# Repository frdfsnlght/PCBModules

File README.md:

# PCBModules
A set of KiCAD 6 schematics and PCB layouts for some handy modules used for electronics projects.

## Available modules

* 8PinHeader

   Useful for plugging in half of a ESP32 CAM module. Includes 2 mounting holes.

* 19PinHeader

   Useful for plugging in half of a typical ESP32 Dev module. Includes 2 mounting holes.

* DrokPowerSupply

   Mount a [Drok Power Regulator](https://smile.amazon.com/dp/B0758ZTS61/) and provide 8 regulated outputs.

More to come...

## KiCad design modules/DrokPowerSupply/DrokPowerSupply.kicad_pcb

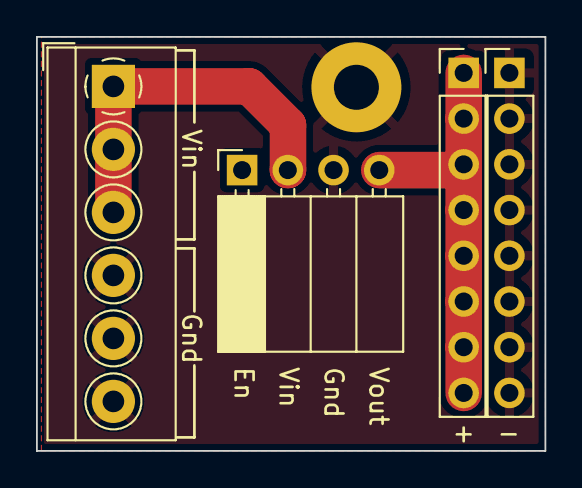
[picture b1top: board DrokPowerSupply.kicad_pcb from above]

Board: 2 copper layers, 28.2 x 23.0 mm, 4 parts (0 on the bottom side), 3 nets.

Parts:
J1: Input; TerminalBlock_4Ucon_1x06_P3.50mm_Horizontal
J2: Drok PS; PinSocket_1x04_P2.54mm_Horizontal
J3: +; PinHeader_1x08_P2.54mm_Vertical
J4: -; PinHeader_1x08_P2.54mm_Vertical

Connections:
/GND: J1.4, J1.5, J1.6, J2.3, J4.1, J4.2, J4.3, J4.4, J4.5, J4.6, J4.7, J4.8
/VIN: J1.1, J1.2, J1.3, J2.2
/VOUT: J2.4, J3.1, J3.2, J3.3, J3.4, J3.5, J3.6, J3.7, J3.8

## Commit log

2022-09-10 Changed
2022-09-10 Added OSHPark template
2022-09-10 Fixed template
2022-09-10 New modules
2022-09-13 Tweaked
2022-09-13 Changed REF names
2022-09-13 Added 8 pin header
